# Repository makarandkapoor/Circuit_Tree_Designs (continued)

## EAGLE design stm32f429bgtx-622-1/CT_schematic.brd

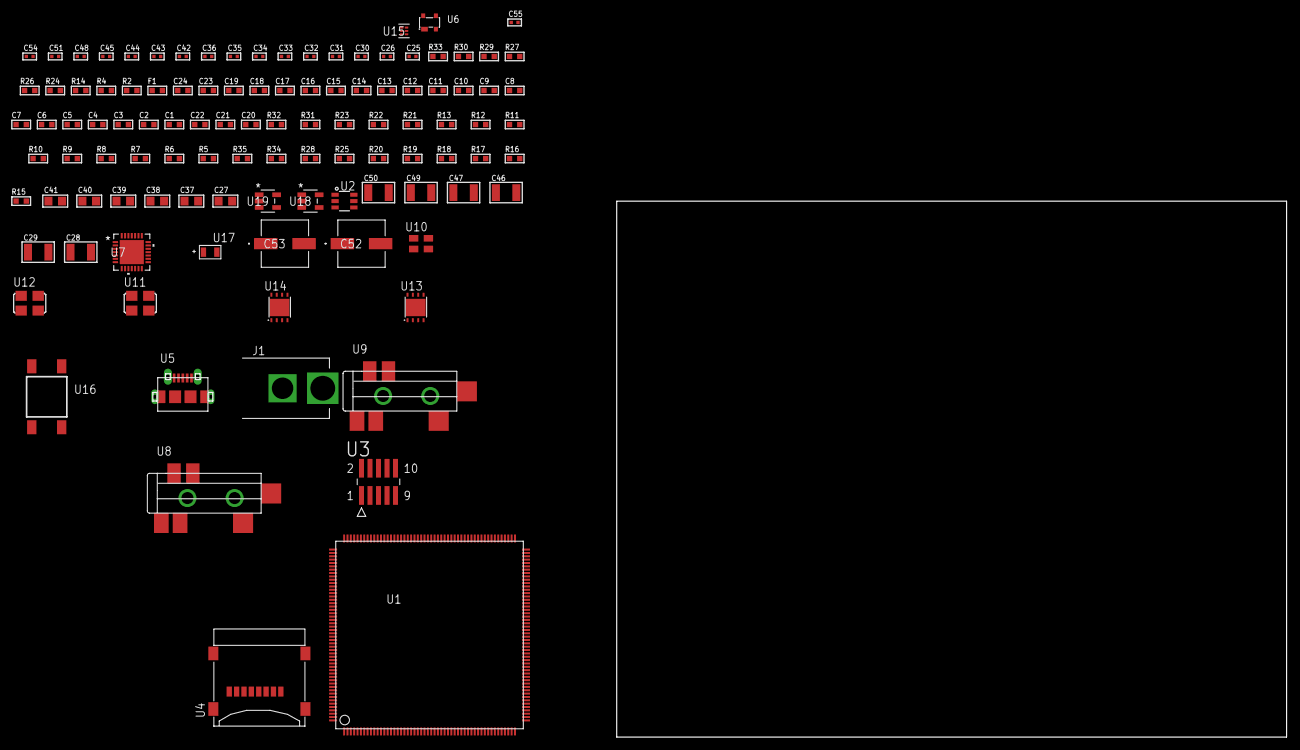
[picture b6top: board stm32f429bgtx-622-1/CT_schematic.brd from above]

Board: 2 copper layers, 109 parts (0 on the bottom side), 51 nets, no tracks yet.

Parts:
C1, C24: 1e-06; C0603
C2, C3, C4, C5, C6, C7, C8, C9, C10, C11, C12, C13, C14, C15, C16, C17, C18, C19: 1e-07; C0603
C20: 4.7e-06; C0603
C21, C22: 2.2e-09; C0603
C23: 1e-08; C0603
C25, C26, C32, C33, C34, C35, C36, C51: 1e-07; C0402
C27, C37, C38, C39, C40, C41: 1e-05; C0805
C28, C29: 2.2e-05; C1210
C30, C31: 1e-09; C0402
C42, C43, C44, C45, C48, C54, C55: 1e-08; C0402
C46, C47, C49, C50: 1e-05; C1210
C52, C53: 0.0001; EXV-9H
F1: 240.0; L0603
J1: PJ-037B; PJ-037B_PACKAGE
R2, R27, R30: 1000.0; R0603
R4: 4700.0; R0603
R5, R21, R22, R23: 47000.0; R0603
R6, R7, R8, R9, R10, R11, R12, R13, R31, R32: 10000.0; R0603
R14: 5.0; R0603
R15, R16, R17, R18, R19, R20, R25, R28: 100000.0; R0603
R24: 680.0; R0603
R26: 2231.0; R0603
R29: 3900.0; R0603
R33: 9100.0; R0603
R34: 680000.0; R0603
R35: 120000.0; R0603
U1: STM32F429BGT6; LQFP208
U2: MAX4995AAUT+T; SOT-23-6
U3: FTSH-105-01-L-DV-K; SAMTEC_FTSH-105-01-L-DV-K
U4: 0472192001; MOLEX_47219-2001
U5: 47590-0001; MICRO_USB_AB
U6: prtr5v0u2ax; SOT143B
U7: WM8731CLSEFL; QFN-28
U8, U9: SJ-43515TS-SMT-TR
U10: ASEK-32.768KHz-ECST; ASEK
U11: ASFL1-12.288MHZ-EC-T; ASFL1
U12: ASFL1-25MHZ-NCS; ASFL1
U13, U14: LP3878SDX-ADJ/NOPB; WSON-8
U15: TPS3895ADRYR; SON-6
U16: 4-1437565-2; SW_4-1437565-2
U17: Q65110A2395; LGM67K-G1J2-24-Z
U18, U19: nc7sz125m5x; NC7SZ125M5X

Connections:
CLK_U1_9: U1.9, U10.3
CLK_U1_32: U1.32, U12.3
CLK_U7_1: U7.1, U11.3
GND: C1.2, C2.2, C3.2, C4.2, C5.2, C6.2, C7.2, C8.2, C9.2, C10.2, C11.2, C12.2, C13.2, C14.2, C15.2, C16.2, C17.2, C18.2, C19.2, C20.2, C21.2, C22.2, C23.2, C24.2, C25.2, C26.2, C27.2, C31.2, C32.2, C33.2, C34.2, C35.2, C36.2, C37.2, C38.2, C39.2, C40.2, C41.2, C42.2, C43.2, C44.2, C45.2, C46.2, C47.2, C48.2, C49.2, C50.2, C51.2, C52.2, C53.2, C54.2, C55.2, J1.2, R2.2, R5.2, R8.2, R10.2, R14.2, R21.2, R22.2, R23.2, R27.2, R30.2, R33.2, R35.2, U1.14, U1.25, U1.40, U1.51, U1.60, U1.72, U1.82, U1.93, U1.114, U1.125, U1.136, U1.149, U1.170, U1.184, U1.202, U2.2, U3.3, U3.5, U4.6, U4.G1, U4.G2, U4.G3, U4.G4, U5.5, U5.6, U5.7, U5.8, U5.9, U6.1, U7.4, U7.15, U7.19, U7.25, U7.26, U7.29, U8.1, U9.1, U10.2, U11.2, U12.2, U13.3, U13.PAD, U14.3, U14.PAD, U15.2, U17.C, U18.2, U18.3, U19.1, U19.3
NET_U1_34: R4.1, U1.34, U19.4
NET_U1_42: C23.1, C24.1, F1.1, U1.41, U1.42
NET_U1_63: R8.1, U1.63
NET_U1_92: C21.1, U1.92
NET_U1_148: C22.1, U1.148
NET_U1_197: R7.1, U1.197
NET_U1_203: R6.1, U1.203
NET_U1_208: U16.3, U16.4
NET_U2_3: R5.1, U2.3
NET_U3_9: R14.1, U3.9
NET_U7_20: C36.1, C41.1, U7.20
NET_U8_2: C29.1, R22.1, U8.2
NET_U8_5: C28.1, R21.1, U8.5
NET_U9_5: C30.1, C31.1, R23.1, R24.1, U9.5
NET_U13_1: C45.1, U13.1
NET_U13_6: R26.2, R27.1, U13.6
NET_U13_8: R25.1, U13.8
NET_U14_1: C48.1, U14.1
NET_U14_6: R29.2, R30.1, U14.6
NET_U14_8: R28.1, U14.8
NET_U15_1: R32.1, R33.1, U15.1
NET_U15_3: R34.2, R35.1, U15.3
NET_U15_4: R31.1, U15.4, U18.4, U19.2
NET_U16_1: R2.1, U16.1, U16.2
PROC_GPIO_TO_U1_USB_FAULT: R9.1, U1.2, U2.6
PROC_GPIO_TO_U1_VBUS_EN: R10.1, U1.1, U2.4
PROC_I2S2_CK: U1.90, U7.7
PROC_I2S2_EXT_SD: U1.37, U7.10
PROC_I2S2_SD: U1.38, U7.8
PROC_I2S2_WS: U1.104, U7.9, U7.11
PROC_SDIO_CK: R16.1, U1.163, U4.5
PROC_SDIO_CMD: R15.1, U1.166, U4.3
PROC_SDIO_D0: R17.1, U1.140, U4.7
PROC_SDIO_D1: R18.1, U1.141, U4.8
PROC_SDIO_D2: R19.1, U1.161, U4.1
PROC_SDIO_D3: R20.1, U1.162, U4.2
PROC_SYS_JTCK_SWCLK: R12.1, U1.159, U3.4
PROC_SYS_JTDO_SWO: U1.192, U3.6
PROC_SYS_JTMS_SWDIO: R13.1, U1.147, U3.2
PROC_USB_OTG_FS_DM: U1.145, U5.2, U6.3
PROC_USB_OTG_FS_DP: U1.146, U5.3, U6.2
PROC_USB_OTG_FS_ID: U1.144, U5.4
PROC_USB_OTG_FS_VBUS: U1.143, U2.1, U5.1, U6.4
RST_OUT_U3_JTAG_RST_B: R11.1, U3.10, U18.1
VCC_S1_11V2: C46.1, C49.1, C52.1, C53.1, J1.1, R25.2, R28.2, U13.4, U14.4
VCC_TIER1_3V3: C1.1, C2.1, C3.1, C4.1, C5.1, C6.1, C7.1, C8.1, C9.1, C10.1, C11.1, C12.1, C13.1, C14.1, C15.1, C16.1, C17.1, C18.1, C19.1, C20.1, C25.1, C26.1, C27.1, C32.1, C33.1, C34.1, C35.1, C37.1, C38.1, C39.1, C40.1, C42.1, C43.1, C44.1, C47.1, C51.1, C54.1, C55.1, F1.2, R4.2, R6.2, R7.2, R9.2, R11.2, R12.2, R13.2, R15.2, R16.2, R17.2, R18.2, R19.2, R20.2, R26.1, R31.2, R32.2, R34.1, U1.6, U1.15, U1.26, U1.39, U1.52, U1.59, U1.73, U1.83, U1.94, U1.103, U1.115, U1.124, U1.137, U1.150, U1.158, U1.171, U1.185, U1.204, U3.1, U4.4, U7.3, U7.5, U7.12, U7.18, U10.4, U11.4, U12.4, U13.5, U15.6, U18.5, U19.5
VCC_TIER1_5V0: C50.1, R29.1, U2.5, U14.5

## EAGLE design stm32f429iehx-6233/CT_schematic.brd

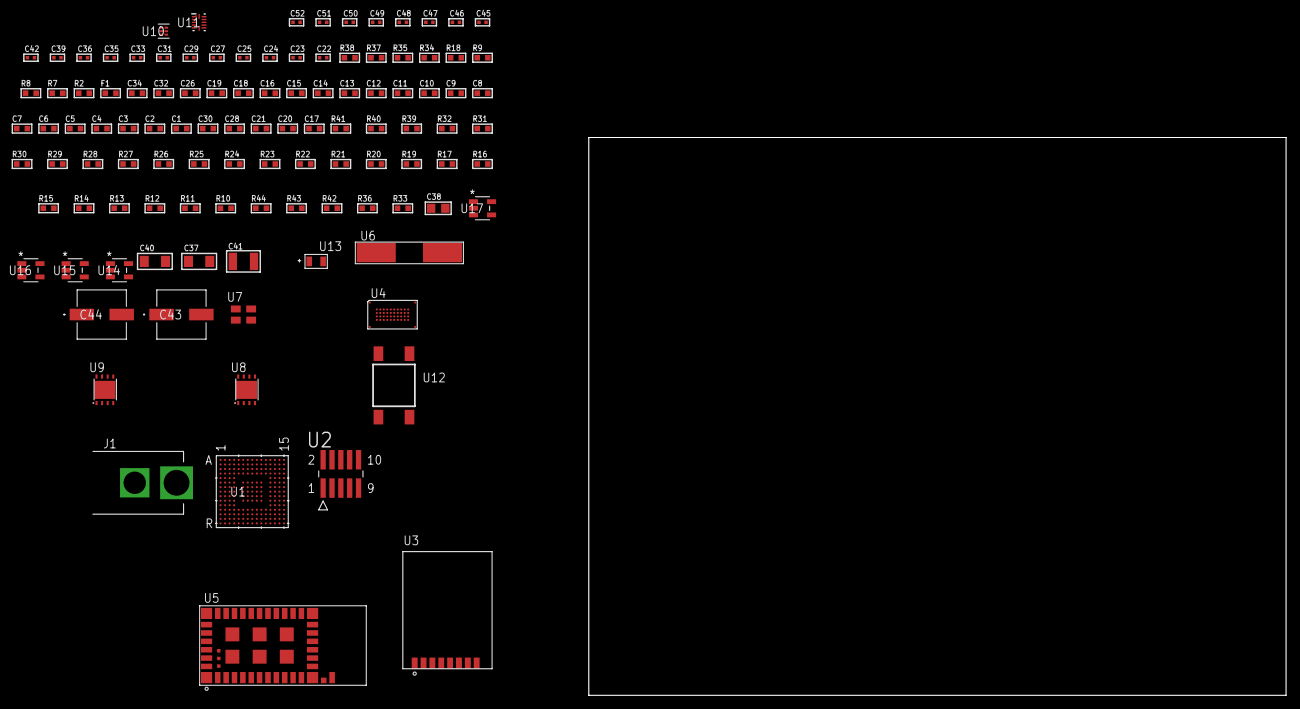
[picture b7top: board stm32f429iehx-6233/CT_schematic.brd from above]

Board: 2 copper layers, 100.0 x 80.0 mm, 110 parts (0 on the bottom side), 78 nets, no tracks yet.

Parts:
C1, C19, C26, C32, C34: 1e-06; C0603
C2, C3, C4, C5, C6, C7, C8, C9, C10, C11, C12, C13, C14, C15, C16: 1e-07; C0603
C17: 4.7e-06; C0603
C18: 1e-08; C0603
C20, C21, C28, C30: 2.2e-06; C0603
C22, C23: 1e-11; C0402
C24, C25, C27, C29, C31, C33, C42, C46, C48: 1e-07; C0402
C35, C36, C39, C45, C47, C49, C50, C51, C52: 1e-08; C0402
C37, C40: 1e-05; C1206
C38: 1e-05; C0805
C41: 1e-05; C1210
C43, C44: 0.0001; EXV-9H
F1: 240.0; L0603
J1: PJ-037B; PJ-037B_PACKAGE
R2, R35, R38: 1000.0; R0603
R7, R8, R9: 4700.0; R0603
R10, R11, R12, R13, R14, R15, R16, R17, R19, R20, R21, R22, R23, R24, R25, R32, R39, R40: 10000.0; R0603
R18: 5.0; R0603
R26, R27, R28, R29, R30, R31: 34000.0; R0603
R33, R36: 100000.0; R0603
R34: 806.0; R0603
R37: 2231.0; R0603
R41: 82000.0; R0603
R42: 300000.0; R0603
R43: 120000.0; R0603
R44: 200000.0; R0603
U1: STM32F429IEH6; UFBGA176_25
U2: FTSH-105-01-L-DV-K; SAMTEC_FTSH-105-01-L-DV-K
U3: RFM75-S
U4: S29VS256RABBHW000
U5: 88-00153-02
U6: ABLS-25.000MHZ-B2F-T
U7: ASEK-32.768KHz-ECST; ASEK
U8, U9: LP3878SDX-ADJ/NOPB; WSON-8
U10: TPS3895ADRYR; SON-6
U11: LSF0204DRUTR; RUT0012A
U12: 4-1437565-2; SW_4-1437565-2
U13: Q65110A2395; LGM67K-G1J2-24-Z
U14, U15, U16, U17: nc7sz125m5x; NC7SZ125M5X

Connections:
CLK_CRYSTAL_U1_G1: C22.1, U1.G1, U6.1
CLK_CRYSTAL_U1_H1: C23.1, U1.H1, U6.2
CLK_U1_E1: U1.E1, U7.3
GND: C1.2, C2.2, C3.2, C4.2, C5.2, C6.2, C7.2, C8.2, C9.2, C10.2, C11.2, C12.2, C13.2, C14.2, C15.2, C16.2, C17.2, C18.2, C19.2, C20.2, C21.2, C22.2, C23.2, C24.2, C25.2, C26.2, C27.2, C28.2, C29.2, C30.2, C31.2, C32.2, C33.2, C34.2, C35.2, C36.2, C37.2, C38.2, C39.2, C40.2, C41.2, C42.2, C43.2, C44.2, C45.2, C46.2, C47.2, C48.2, C49.2, C50.2, C51.2, C52.2, J1.2, R2.2, R13.2, R17.2, R18.2, R32.2, R35.2, R38.2, R41.2, R43.2, U1.D5, U1.D7, U1.D8, U1.D9, U1.F2, U1.F6, U1.F7, U1.F8, U1.F9, U1.F10, U1.F12, U1.G2, U1.G6, U1.G7, U1.G8, U1.G9, U1.G10, U1.G12, U1.H6, U1.H7, U1.H8, U1.H9, U1.H10, U1.H12, U1.J6, U1.J7, U1.J8, U1.J9, U1.J10, U1.K6, U1.K7, U1.K8, U1.K9, U1.K10, U1.M1, U1.M8, U1.M9, U1.N1, U2.3, U2.5, U3.1, U4.C5, U4.D12, U4.E3, U4.F5, U5.1, U5.9, U5.13, U5.14, U5.15, U5.16, U5.17, U5.18, U5.19, U5.20, U5.21, U5.22, U5.23, U5.24, U5.25, U5.26, U5.27, U5.31, U5.32, U5.39, U5.40, U5.41, U5.42, U5.43, U5.44, U5.49, U7.2, U8.3, U8.PAD, U9.3, U9.PAD, U10.2, U11.6, U13.C, U14.2, U14.3, U15.1, U15.3, U16.1, U16.3, U17.1, U17.3
NET_U1_C6: R10.1, U1.C6
NET_U1_D6: R11.1, U1.D6
NET_U1_F13: C21.1, U1.F13
NET_U1_J1: R9.1, U1.J1, U17.4
NET_U1_L4: R13.1, U1.L4
NET_U1_M6: R12.1, U1.M6
NET_U1_M10: C20.1, U1.M10
NET_U1_R1: C18.1, C19.1, F1.1, U1.P1, U1.R1
NET_U1_R15: U12.3, U12.4
NET_U2_9: R18.1, U2.9
NET_U3_3: R19.1, U3.3
NET_U4_D8: R7.1, U4.D8, U15.4
NET_U5_6: R32.1, U5.6
NET_U5_10: R8.1, U5.10, U16.4
NET_U5_11: R25.1, U5.11
NET_U8_1: C36.1, U8.1
NET_U8_6: R34.2, R35.1, U8.6
NET_U8_8: R33.1, U8.8
NET_U9_1: C39.1, U9.1
NET_U9_6: R37.2, R38.1, U9.6
NET_U9_8: R36.1, U9.8
NET_U10_1: R40.1, R41.1, U10.1
NET_U10_3: R42.2, R43.1, U10.3
NET_U10_4: R39.1, U10.4, U14.4, U15.2, U16.2, U17.2
NET_U11_12: R44.1, U11.12
NET_U12_1: R2.1, U12.1, U12.2
PROC_FMC_A16: U1.N14, U4.D4
PROC_FMC_A17: U1.N13, U4.C11
PROC_FMC_A18: U1.M15, U4.D10
PROC_FMC_A19: U1.A1, U4.C10
PROC_FMC_A20: U1.B1, U4.D5
PROC_FMC_A21: U1.B2, U4.C4
PROC_FMC_A22: U1.B3, U4.C12
PROC_FMC_A23: U1.A2, U4.D7
PROC_FMC_CLK: U1.D11, U4.C6
PROC_FMC_D0: U1.M14, U4.F3
PROC_FMC_D1: U1.L14, U4.F4
PROC_FMC_D2: U1.B12, U4.E6
PROC_FMC_D3: U1.C12, U4.E7
PROC_FMC_D4: U1.R8, U4.F8
PROC_FMC_D5: U1.P8, U4.F9
PROC_FMC_D6: U1.P9, U4.E10
PROC_FMC_D7: U1.R9, U4.E11
PROC_FMC_D8: U1.P10, U4.E4
PROC_FMC_D9: U1.R10, U4.E5
PROC_FMC_D10: U1.N11, U4.F6
PROC_FMC_D11: U1.P11, U4.F7
PROC_FMC_D12: U1.R11, U4.E8
PROC_FMC_D13: U1.P15, U4.E9
PROC_FMC_D14: U1.P14, U4.F11
PROC_FMC_D15: U1.N15, U4.F12
PROC_FMC_NE2: R22.1, U1.C10, U4.D11
PROC_FMC_NL: U1.B5, U4.D6
PROC_FMC_NOE: R24.1, U1.D10, U4.E12
PROC_FMC_NWAIT: R21.1, U1.B11, U4.C3
PROC_FMC_NWE: R23.1, U1.C11, U4.C8
PROC_SDIO_CK: R31.1, U1.A12, U5.36
PROC_SDIO_CMD: R30.1, U1.D12, U5.37
PROC_SDIO_D0: R26.1, U1.G14, U5.35
PROC_SDIO_D1: R27.1, U1.F14, U5.34
PROC_SDIO_D2: R28.1, U1.B14, U5.2
PROC_SDIO_D3: R29.1, U1.B13, U5.38
PROC_SPI1_MISO_TOXCVR: U3.7, U11.7
PROC_SPI1_MOSI_TOXCVR: U3.6, U11.8
PROC_SPI1_NSS_TOXCVR: R20.1, U3.4, U11.9
PROC_SPI1_SCK_TOXCVR: U3.5, U11.10
PROC_SYS_JTCK_SWCLK: R17.1, U1.A14, U2.4
PROC_SYS_JTDI: R15.1, U1.A13, U2.8
PROC_SYS_JTDO_SWO: U1.A10, U2.6
PROC_SYS_JTMS_SWDIO: R16.1, U1.A15, U2.2
RST_OUT_U2_JTAG_RST_B: R14.1, U2.10, U14.1
VCC_S1_10V7: C37.1, C40.1, C43.1, C44.1, J1.1, R33.2, R36.2, U8.4, U9.4
VCC_TIER1_1V8: C1.1, C2.1, C3.1, C4.1, C5.1, C6.1, C7.1, C8.1, C9.1, C10.1, C11.1, C12.1, C13.1, C14.1, C15.1, C16.1, C17.1, C24.1, C27.1, C28.1, C29.1, C30.1, C33.1, C34.1, C38.1, C42.1, C47.1, C48.1, C49.1, C50.1, C51.1, C52.1, F1.2, R7.2, R8.2, R9.2, R10.2, R11.2, R12.2, R14.2, R15.2, R16.2, R21.2, R22.2, R23.2, R24.2, R25.2, R26.2, R27.2, R28.2, R29.2, R30.2, R31.2, R34.1, R39.2, R40.2, R42.1, R44.2, U1.C1, U1.C5, U1.C7, U1.C8, U1.C9, U1.F3, U1.G3, U1.G13, U1.H13, U1.J12, U1.J13, U1.K4, U1.N8, U1.N9, U1.N10, U2.1, U4.C7, U4.D3, U4.F10, U5.33, U8.5, U10.6, U11.1, U14.5, U15.5, U16.5, U17.5
VCC_TIER1_3V3: C25.1, C26.1, C31.1, C32.1, C35.1, C41.1, C45.1, C46.1, R19.2, R20.2, R37.1, U3.2, U5.12, U7.4, U9.5, U11.11
